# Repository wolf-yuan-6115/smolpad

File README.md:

# SmolPad

A slightly customized PCB keyboard with a case. 

> [Schematic download](pcb/schematic.pdf)

> Bottom lighting design is inspired by [samdev-7/squarepad](https://github.com/samdev-7/squarepad)
>
> Uses external 3D component, https://makerworld.com/en/models/628840-ec11-encoder-knob#profileId-593261.

## Bill of material

| Item                   | QTY. |
|------------------------|:----:|
| Seeed Xiao RP2040      | 1    |
| SK6812 mini-e          | 12   |
| MX style switches      | 8    |
| EC11E Rotatory encoder | 1    |
| 0.91" OLED screen      | 1    |
| 1N4148 Diode           | 9    |

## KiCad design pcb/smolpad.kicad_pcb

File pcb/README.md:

# smolpad/pcb

This folder contains everything that's designed with KiCad.

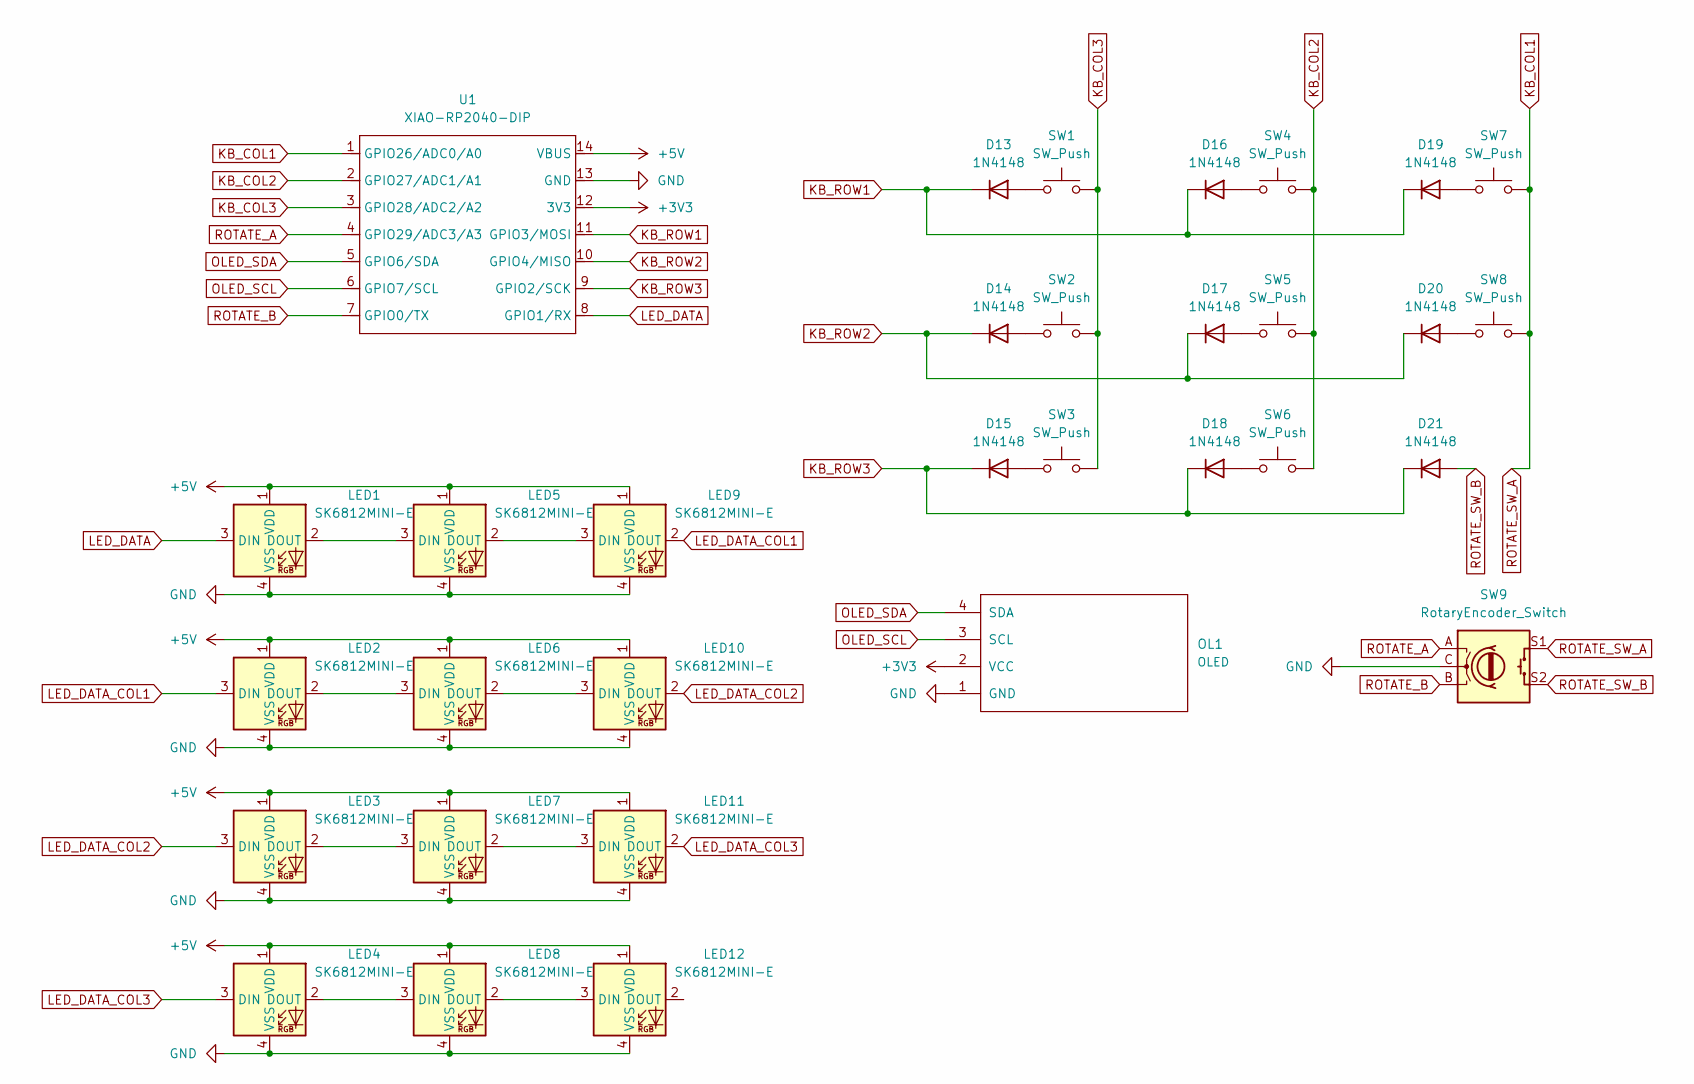
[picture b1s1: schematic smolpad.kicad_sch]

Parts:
D13, D14, D15, D16, D17, D18, D19, D20, D21: 1N4148; D_DO-35_SOD27_P7.62mm_Horizontal
LED1, LED2, LED3, LED4, LED5, LED6, LED7, LED8, LED9, LED10, LED11, LED12: SK6812MINI-E; LED_6028R
OL1: OLED; SSD1306-0.91-OLED-4pin-128x32
SW1, SW2, SW3, SW4, SW5, SW6, SW7, SW8: SW_Push; SW_Cherry_MX_1.00u_PCB_1
SW9: RotaryEncoder_Switch; RotaryEncoder_Alps_EC11E-Switch_Vertical_H20mm
U1: XIAO-RP2040-DIP

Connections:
+3V3: OL1.2 (VCC), U1.12 (3V3)
+5V: LED1.1 (VDD), LED2.1 (VDD), LED3.1 (VDD), LED4.1 (VDD), LED5.1 (VDD), LED6.1 (VDD), LED7.1 (VDD), LED8.1 (VDD), LED9.1 (VDD), LED10.1 (VDD), LED11.1 (VDD), LED12.1 (VDD), U1.14 (VBUS)
GND: LED1.4 (VSS), LED2.4 (VSS), LED3.4 (VSS), LED4.4 (VSS), LED5.4 (VSS), LED6.4 (VSS), LED7.4 (VSS), LED8.4 (VSS), LED9.4 (VSS), LED10.4 (VSS), LED11.4 (VSS), LED12.4 (VSS), OL1.1 (GND), SW9.C, U1.13 (GND)
KB_COL1: SW7.2, SW8.2, SW9.S1, U1.1 (GPIO26/ADC0/A0)
KB_COL2: SW4.2, SW5.2, SW6.2, U1.2 (GPIO27/ADC1/A1)
KB_COL3: SW1.2, SW2.2, SW3.2, U1.3 (GPIO28/ADC2/A2)
KB_ROW1: D13.1 (K), D16.1 (K), D19.1 (K), U1.11 (GPIO3/MOSI)
KB_ROW2: D14.1 (K), D17.1 (K), D20.1 (K), U1.10 (GPIO4/MISO)
KB_ROW3: D15.1 (K), D18.1 (K), D21.1 (K), U1.9 (GPIO2/SCK)
LED_DATA: LED1.3 (DIN), U1.8 (GPIO1/RX)
LED_DATA_COL1: LED2.3 (DIN), LED9.2 (DOUT)
LED_DATA_COL2: LED3.3 (DIN), LED10.2 (DOUT)
LED_DATA_COL3: LED4.3 (DIN), LED11.2 (DOUT)
unnamed: D13.2 (A), SW1.1
unnamed: D14.2 (A), SW2.1
unnamed: D15.2 (A), SW3.1
unnamed: D16.2 (A), SW4.1
unnamed: D17.2 (A), SW5.1
unnamed: D18.2 (A), SW6.1
unnamed: D19.2 (A), SW7.1
unnamed: D20.2 (A), SW8.1
unnamed: LED1.2 (DOUT), LED5.3 (DIN)
unnamed: LED2.2 (DOUT), LED6.3 (DIN)
unnamed: LED3.2 (DOUT), LED7.3 (DIN)
unnamed: LED4.2 (DOUT), LED8.3 (DIN)
unnamed: LED5.2 (DOUT), LED9.3 (DIN)
unnamed: LED6.2 (DOUT), LED10.3 (DIN)
unnamed: LED7.2 (DOUT), LED11.3 (DIN)
unnamed: LED8.2 (DOUT), LED12.3 (DIN)
OLED_SCL: OL1.3 (SCL), U1.6 (GPIO7/SCL)
OLED_SDA: OL1.4 (SDA), U1.5 (GPIO6/SDA)
ROTATE_A: SW9.A, U1.4 (GPIO29/ADC3/A3)
ROTATE_B: SW9.B, U1.7 (GPIO0/TX)
ROTATE_SW_B: D21.2 (A), SW9.S2

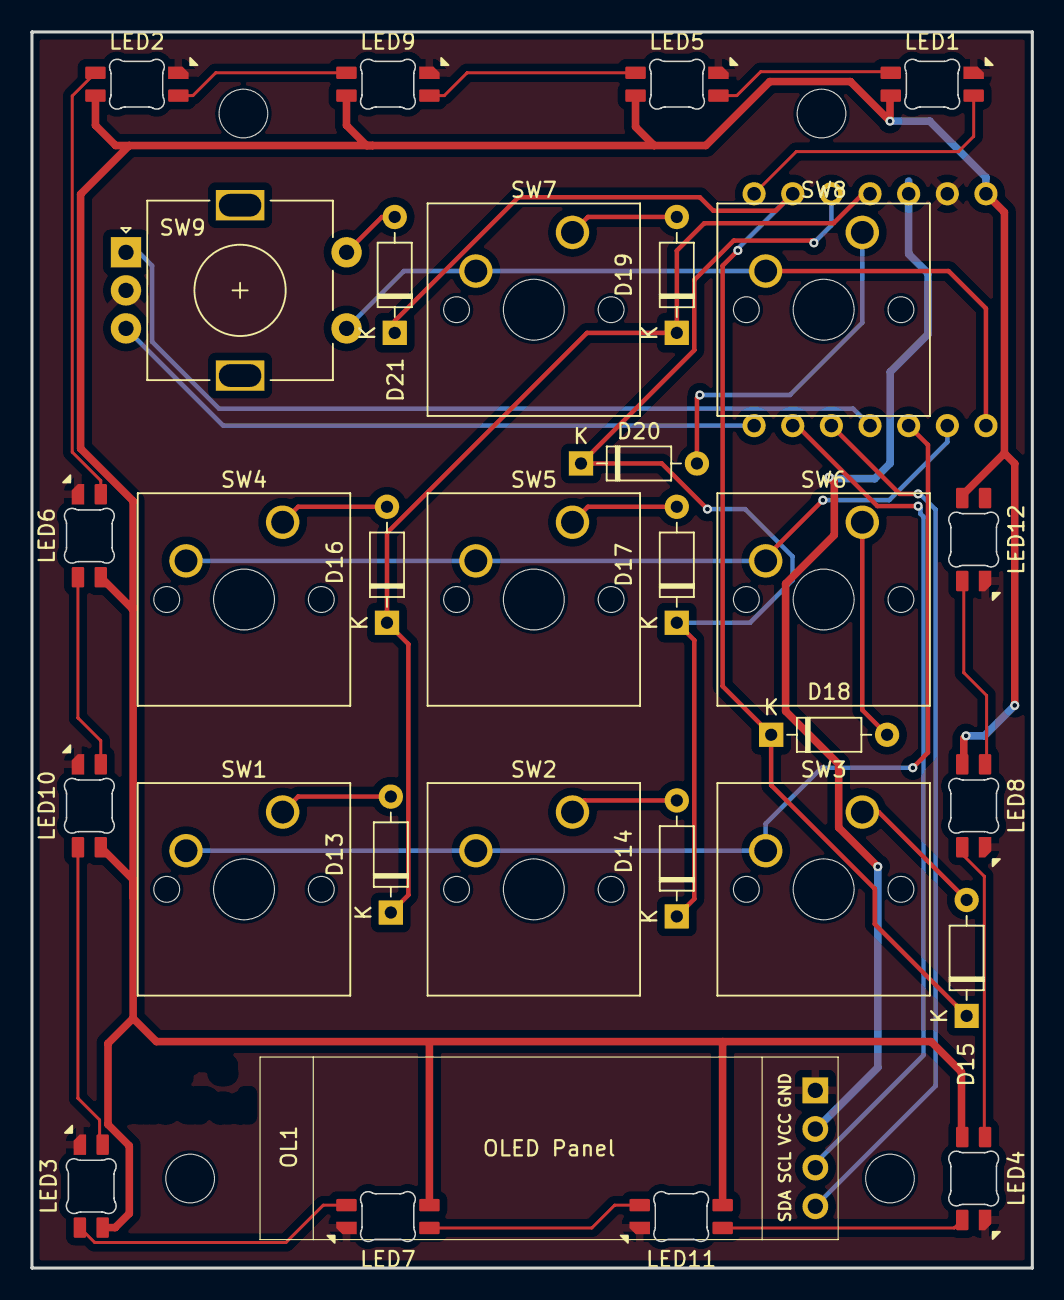
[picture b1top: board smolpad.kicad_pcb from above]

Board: 2 copper layers, 65.8 x 81.2 mm, 32 parts (1 on the bottom side), 34 nets.

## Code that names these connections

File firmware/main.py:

# A "should" work firmware, might subject to change in the future

import board
from kmk.kmk_keyboard import KMKKeyboard
from kmk.keys import KC
from kmk.scanners import DiodeOrientation
from kmk.modules.encoder import EncoderHandler
from kmk.modules.oled import OLED, OLEDScreen
from kmk.extensions.rgb import RGB

keyboard = KMKKeyboard()

keyboard.col_pins = (board.GP26, board.GP27, board.GP28)  # KB_COL1~3
keyboard.row_pins = (board.GP3, board.GP4, board.GP2)  # KB_ROW1~3
keyboard.diode_orientation = DiodeOrientation.COL2ROW

keyboard.keymap = [
    [
        KC.A, KC.B, KC.C,
        KC.D, KC.E, KC.F,
        KC.G, KC.H, KC.NO
    ]
]

encoder = EncoderHandler()
encoder.pins = ((board.GP0, board.GP29, None),)  # ROTATE_A, ROTATE_B, no switch
encoder.map = [
    (lambda: keyboard.send(KC.VOLD), lambda: keyboard.send(KC.VOLU))
]
keyboard.modules.append(encoder)

oled = OLED(
    rotation=OLEDRotation.ROT_0,
    sda=board.GP6,  # OLED_SDA
    scl=board.GP7,  # OLED_SCL
)
oled.init_display()
oled.set_display_content(
    OLEDScreen(lambda: ['Hello World', 'KMK Firmware'])
)
keyboard.modules.append(oled)

rgb = RGB(
    pixel_pin=board.GP1,  # LED_DATA
    num_pixels=12,         # Total number of SK6812Mini-E
    rgb_order=(1, 0, 2),   # Usually GRB, but double-check yours!
    auto_update=True
)
rgb.effect = "rainbow"
keyboard.extensions.append(rgb)

if __name__ == '__main__':
    keyboard.go()

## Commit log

2025-06-25 feat: add readme
2025-06-25 feat: add cad files
2025-06-25 feat: add pcb
2025-06-25 feat: add stp files for 3d printing
2025-06-25 feat: add gerber
2025-06-25 feat: add firmware
2025-06-25 feat: add schematic to readme
2025-06-26 feat: update oled display driver
2025-06-26 feat: add branding to case
2025-06-27 fix: accidently made my oled 0.91 foot not inch
2025-06-28 fix: increase hole length to prevent pcb wiggle
2025-06-28 fix: unconnected trace on pcb
2025-07-16 feat: update board
2025-07-16 feat: update readme
2025-07-20 feat: add firmware to production folder
2025-08-11 feat: update case 3d file
2025-09-13 feat: update to latest firmware
